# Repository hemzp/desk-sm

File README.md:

# desk-sm — a small monitor for my desk

A custom PCB that sits on my desk and shows the album art of whatever I'm playing on Spotify, spinning like a vinyl while the song plays and freezing when it's paused. It also doubles as a weather display and a daily calendar view, controlled with two push buttons and a rotary encoder.

*Front: display, two push buttons, and the rotary encoder.*

*Back: mounting holes and through-hole pads for the controls.*

## What it does

- **Now playing**: pulls the current track from the Spotify API and shows the album art. The art rotates like a vinyl record while the song plays, and stops when it's paused.
- **Weather**: a dedicated screen, because it's Seattle and I need to know if it's raining or not raining.
- **Calendar**: shows the day's schedule, class times, office hours, extracurriculars, meetings, whatever's on deck.
- **Controls**: two push buttons handle skip and play/pause. The rotary encoder cycles between the three screens (now playing, weather, calendar).

## Why I built this

I listen to a lot of music and love album art, so a little screen dedicated to it felt like an easy yes. Weather and calendar earned their spot because they're the two things I actually check every morning in college, class times, meetings, and whether Seattle is doing its usual thing.

Mostly, though, I wanted to build something I hadn't done before, hardware end to end, and use the last 10 days of summer break to do it. I also had a free trial of GitHub Copilot's agent and wanted to see what it could actually do: it handled the schematic well when I gave it clear specs, but the KiCad MCP fell apart at placement and routing. I ended up doing that part by hand, which the small scale of this board made manageable, and honestly more satisfying.

## Hardware

- **MCU**: Seeed Studio XIAO ESP32-S3
- **Display**: Adafruit 1.3" 240x240 IPS TFT (ST7789)
- **Controls**: 2x 6mm tactile switches, 1x EC11 rotary encoder
- **PCB**: 2-layer, hand-routed in KiCad

## Status

- [x] Schematic (Copilot-assisted)
- [x] PCB layout and hand-routing
- [x] DRC clean
- [x] Fab files generated, PCB ordered via JLCPCB
- [x] Display ordered from Adafruit
- [x] MCU sourced from Amazon
- [ ] Firmware (display driver, Spotify/weather/calendar integration)
- [ ] Solder and bring-up once the PCB arrives
- [ ] 3D-printed enclosure, designed in FreeCAD, printed on campus at UW

## Next steps

Once the display and MCU land, I'll write and test the firmware, display driving, Spotify polling, weather and calendar pulls, before any of it touches the actual board. When the PCB arrives, I'll solder everything on, take careful measurements, and design an enclosure in FreeCAD to print at one of UW's shops.

There's also a v2 in the back of my mind, more sophisticated, but v1 has to actually work first.

## Want one?

If you see this running and like it, let me know. I can put together a few more, up to 4, you'd just need to source a display and MCU (easy, both off-the-shelf), and I'll get the switches and encoder, solder the board, and flash the firmware. Plug and play from there.

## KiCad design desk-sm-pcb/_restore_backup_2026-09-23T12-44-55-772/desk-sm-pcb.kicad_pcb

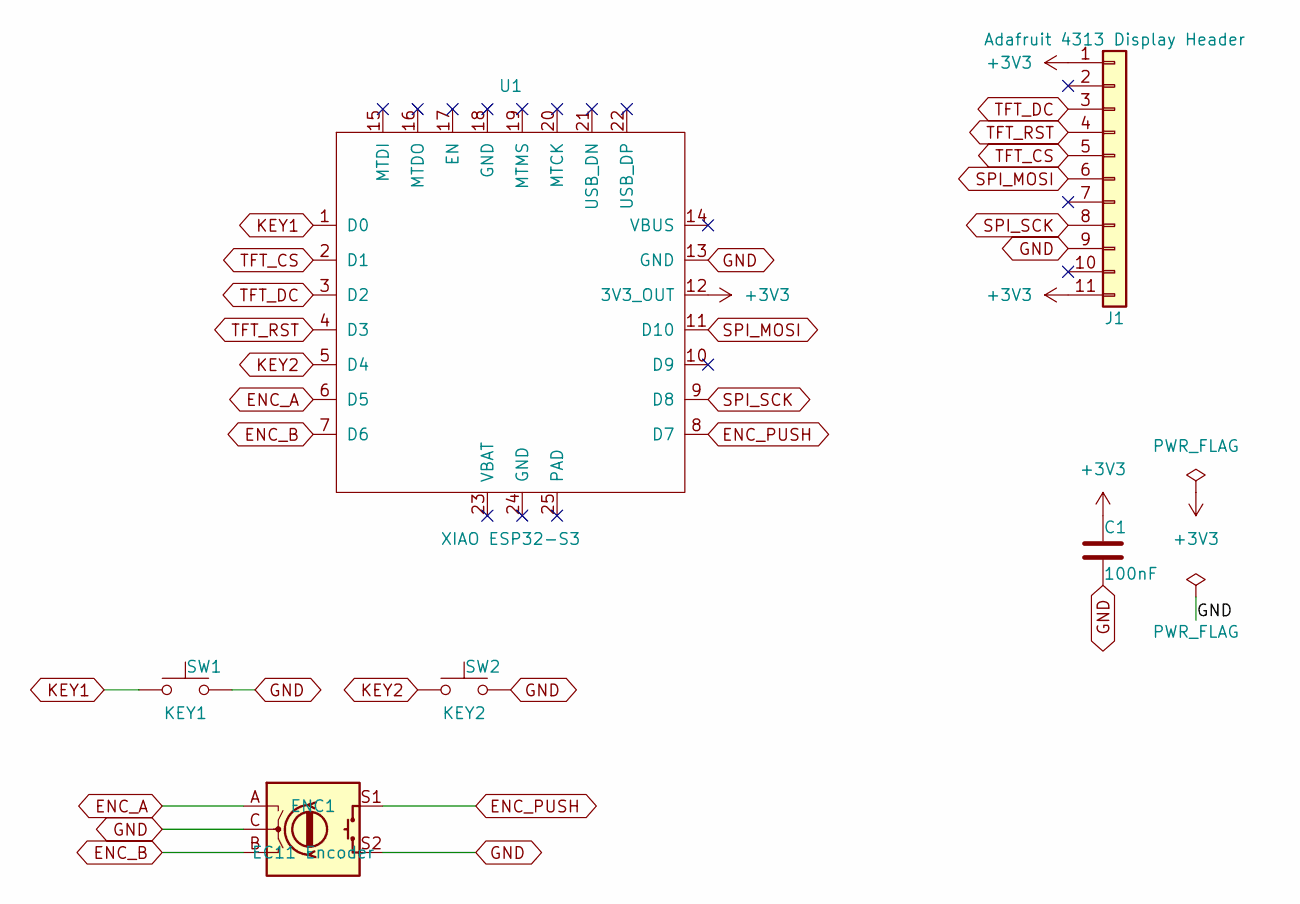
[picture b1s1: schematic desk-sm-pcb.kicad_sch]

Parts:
C1: 100nF; C_Disc_D5.0mm_W2.5mm_P5.00mm
ENC1: EC11 Encoder; EC11_Custom_5Pin
J1: Adafruit 4313 Display Header; Adafruit_4313_Header_1x11_P2.54mm
SW1: KEY1; SW_Push_6mm_Custom
SW2: KEY2; SW_Push_6mm_Custom
U1: XIAO ESP32-S3; XIAO-ESP32-S3-SMD

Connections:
+3V3: C1.1, J1.1, J1.11, U1.12 (3V3_OUT)
ENC_A: ENC1.A, U1.6 (D5)
ENC_B: ENC1.B, U1.7 (D6)
ENC_PUSH: ENC1.S1, U1.8 (D7)
GND: C1.2, ENC1.C, ENC1.S2, J1.9, SW1.2, SW2.2, U1.13 (GND)
KEY1: SW1.1, U1.1 (D0)
KEY2: SW2.1, U1.5 (D4)
SPI_MOSI: J1.6, U1.11 (D10)
SPI_SCK: J1.8, U1.9 (D8)
TFT_CS: J1.5, U1.2 (D1)
TFT_DC: J1.3, U1.3 (D2)
TFT_RST: J1.4, U1.4 (D3)

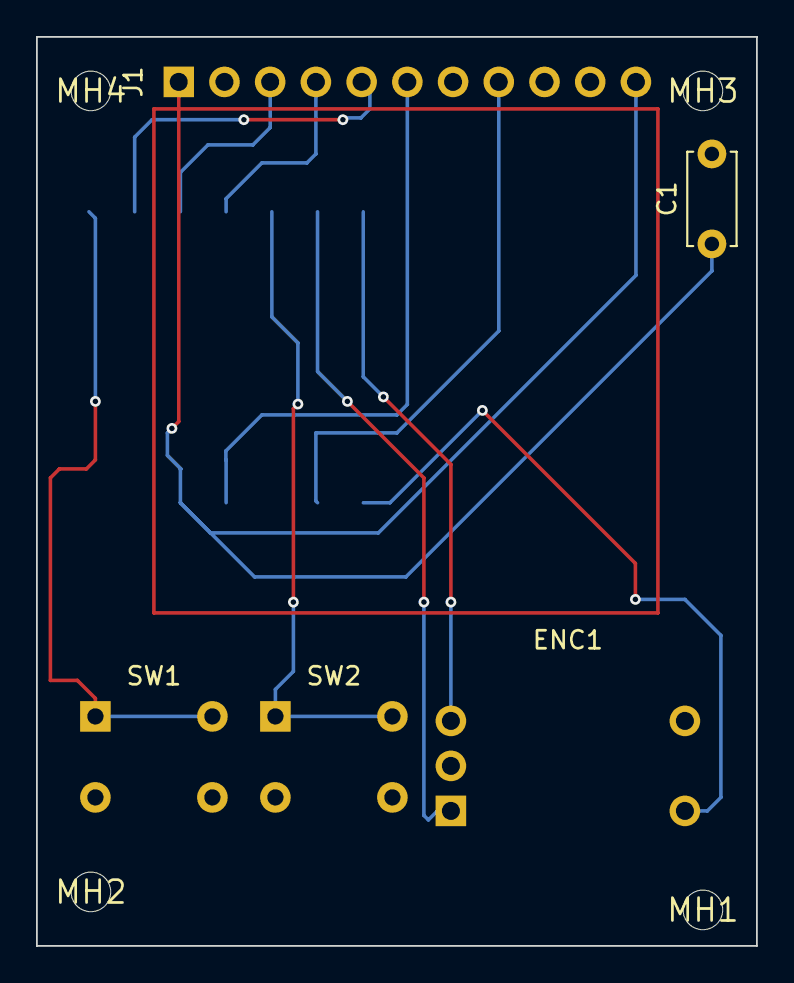
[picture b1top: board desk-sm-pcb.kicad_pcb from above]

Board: 2 copper layers, 40.0 x 50.5 mm, 10 parts (1 on the bottom side), 12 nets.

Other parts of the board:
MH1, MH2, MH3, MH4: MountingHole_2.2mm
